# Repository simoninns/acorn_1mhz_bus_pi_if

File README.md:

# Overview
This project provides a Pi Zero hat which allows a Raspberry Pi to be connected to a BBC Micro or Master via the 1 MHz bus port.  The hat is compatible with all versions of the Raspberry Pi (with 40 pin GPIO headers)

Since the BBC Micro is 5Vs and the Pi is 3.3Vs bi-directional level shifting is required.  In addition, the board provides an active audio buffer to allow the Pi Zero to output audio via the GPIO header.  Audio is routed into the BBC Micro if the audio jack isn't required.

# Production
Production files for JLCPCB.com are included for both the PCB and component assembly.  A custom DRC is also included that checks the project files against JLC's production rules.  Production files can be found in the repo:

https://github.com/simoninns/acorn_1mhz_bus_pi_if/tree/main/kicad/jlcpcb

# Use with Raspberry Pi 3B+
Some Raspberry Pi models will not boot due to leakage on the 3.3V rails - the project provides a jumper that can be set if you want to use on of the affected models.  JP3 pins 1 to 2 should be cut and a solder blob placed on 2-3.  Please see the schematic for details.

# Removal of active audio
To lower production cost the on-board LDO and buffer ICs can be omitted (as well as the audio jack).  Bridging JP1 and JP2 will bypass the active components and provide only a passive audio filter (this works fine but provides a poorer sound quality).

## Project status
This project is at first release.  Please read the wiki and see YouTube for consruction videos (detailed in the wiki also).

## Author
This project is designed and maintained by Simon Inns with help from Dominic Plunkett and Daniel Jameson.

## Software License (GPLv3)

    This is free software: you can redistribute it and/or modify
    it under the terms of the GNU General Public License as published by
    the Free Software Foundation, either version 3 of the License, or
    (at your option) any later version.

    Valiant Turtle 2 is distributed in the hope that it will be useful,
    but WITHOUT ANY WARRANTY; without even the implied warranty of
    MERCHANTABILITY or FITNESS FOR A PARTICULAR PURPOSE.  See the
    GNU General Public License for more details.

    You should have received a copy of the GNU General Public License
    along with this program.  If not, see <http://www.gnu.org/licenses/>.

## Hardware License (Creative Commons BY-SA 4.0)
Please see the following link for details: https://creativecommons.org/licenses/by-sa/4.0/

You are free to:

Share - copy and redistribute the material in any medium or format
Adapt - remix, transform, and build upon the material
for any purpose, even commercially.

This license is acceptable for Free Cultural Works.

The licensor cannot revoke these freedoms as long as you follow the license terms.

Under the following terms:

Attribution - You must give appropriate credit, provide a link to the license, and indicate if changes were made. You may do so in any reasonable manner, but not in any way that suggests the licensor endorses you or your use.

ShareAlike - If you remix, transform, or build upon the material, you must distribute your contributions under the same license as the original.

No additional restrictions - You may not apply legal terms or technological measures that legally restrict others from doing anything the license permits.

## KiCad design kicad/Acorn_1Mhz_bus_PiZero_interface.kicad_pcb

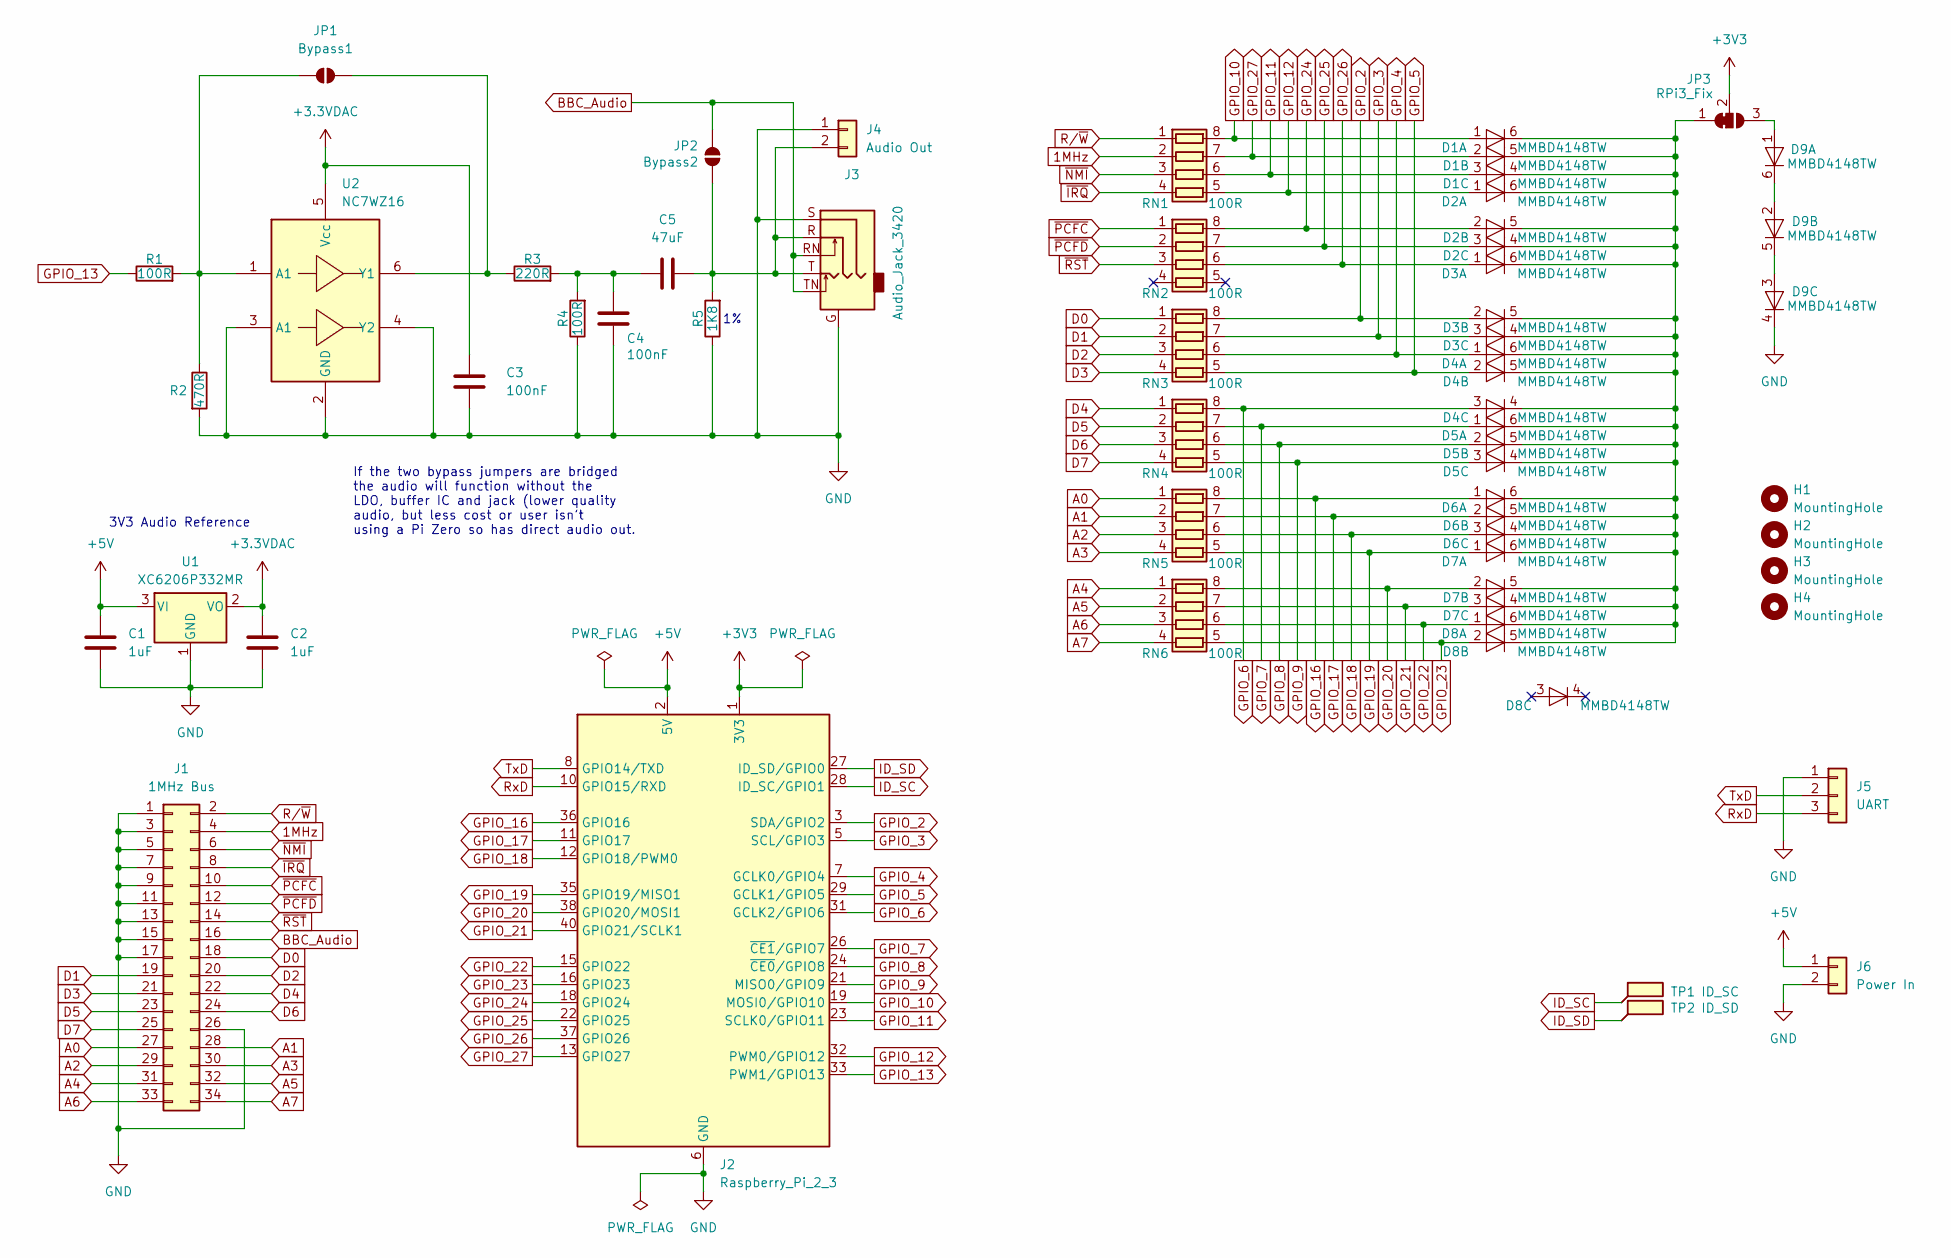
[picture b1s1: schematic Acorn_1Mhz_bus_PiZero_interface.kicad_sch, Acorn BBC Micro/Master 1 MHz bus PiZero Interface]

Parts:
C1, C2: 1uF; C_0603_1608Metric; LCSC C15849
C3, C4: 100nF; C_0603_1608Metric; LCSC C14663
C5: 47uF; C_0603_1608Metric; LCSC C140782
D1, D2, D3, D4, D5, D6, D7, D8, D9: MMBD4148TW; SOT-363_SC-70-6; LCSC C157538
H1, H2, H3, H4: MountingHole; MountingHole_2.7mm_M2.5_DIN965
J1: 1MHz Bus; IDC-Header_2x17_P2.54mm_Vertical; LCSC C20920
J2: Raspberry_Pi_2_3; PinSocket_2x20_P2.54mm_Vertical
J3: Audio_Jack_3420; PJ-3420-X-SMT; LCSC C319102
J4: Audio Out; PinHeader_1x02_P2.54mm_Vertical
J5: UART; PinHeader_1x03_P2.54mm_Vertical
J6: Power In; JST_EH_S2B-EH_1x02_P2.50mm_Horizontal; LCSC C514173
JP1: Bypass1; SolderJumper-2_P1.3mm_Open_Pad1.0x1.5mm
JP2: Bypass2; SolderJumper-2_P1.3mm_Open_Pad1.0x1.5mm
JP3: RPi3_Fix; SolderJumper-3_P1.3mm_Bridged12_Pad1.0x1.5mm_NumberLabels
R1, R4: 100R; R_0603_1608Metric; LCSC C105588
R2: 470R; R_0603_1608Metric; LCSC C114433
R3: 220R; R_0603_1608Metric; LCSC C107696
R5: 1K8; R_0603_1608Metric; LCSC C113298
RN1, RN2, RN3, RN4, RN5, RN6: 100R; R_Array_Convex_4x0402; LCSC C326873
TP1: ID_SC; TestPoint_Pad_1.0x1.0mm
TP2: ID_SD; TestPoint_Pad_1.0x1.0mm
U1: XC6206P332MR; SOT-23-3; LCSC C5446
U2: NC7WZ16; SOT-363_SC-70-6; LCSC C5207819

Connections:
1MHz: J1.4, RN1.2 (R2.1)
+3.3VDAC: C2.1, C3.1, U1.2 (VO), U2.5 (Vcc)
+3V3: J2.1 (3V3), J2.17 (3V3), JP3.2 (C)
+5V: C1.1, J2.2 (5V), J2.4 (5V), J6.1, U1.3 (VI)
A0: J1.27, RN5.1 (R1.1)
A1: J1.28, RN5.2 (R2.1)
A2: J1.29, RN5.3 (R3.1)
A3: J1.30, RN5.4 (R4.1)
A4: J1.31, RN6.1 (R1.1)
A5: J1.32, RN6.2 (R2.1)
A6: J1.33, RN6.3 (R3.1)
A7: J1.34, RN6.4 (R4.1)
BBC_Audio: J1.16, J3.RN, J3.TN, JP2.2 (B)
D0: J1.18, RN3.1 (R1.1)
D1: J1.19, RN3.2 (R2.1)
D2: J1.20, RN3.3 (R3.1)
D3: J1.21, RN3.4 (R4.1)
D4: J1.22, RN4.1 (R1.1)
D5: J1.23, RN4.2 (R2.1)
D6: J1.24, RN4.3 (R3.1)
D7: J1.25, RN4.4 (R4.1)
GND: C1.2, C2.2, C3.2, C4.2, D9.4 (K), J1.1, J1.3, J1.5, J1.7, J1.9, J1.11, J1.13, J1.15, J1.17, J1.26, J2.6 (GND), J2.9 (GND), J2.14 (GND), J2.20 (GND), J2.25 (GND), J2.30 (GND), J2.34 (GND), J2.39 (GND), J3.G, J3.S, J4.1, J5.1, J6.2, R2.2, R4.1, R5.1, U1.1 (GND), U2.2 (GND), U2.3 (A1), U2.4 (Y2)
GPIO_2: D3.2 (A), J2.3 (SDA/GPIO2), RN3.8 (R1.2)
GPIO_3: D3.3 (A), J2.5 (SCL/GPIO3), RN3.7 (R2.2)
GPIO_4: D4.1 (A), J2.7 (GCLK0/GPIO4), RN3.6 (R3.2)
GPIO_5: D4.2 (A), J2.29 (GCLK1/GPIO5), RN3.5 (R4.2)
GPIO_6: D4.3 (A), J2.31 (GCLK2/GPIO6), RN4.8 (R1.2)
GPIO_7: D5.1 (A), J2.26 (~CE1/GPIO7), RN4.7 (R2.2)
GPIO_8: D5.2 (A), J2.24 (~CE0/GPIO8), RN4.6 (R3.2)
GPIO_9: D5.3 (A), J2.21 (MISO0/GPIO9), RN4.5 (R4.2)
GPIO_10: D1.1 (A), J2.19 (MOSI0/GPIO10), RN1.8 (R1.2)
GPIO_11: D1.3 (A), J2.23 (SCLK0/GPIO11), RN1.6 (R3.2)
GPIO_12: D2.1 (A), J2.32 (PWM0/GPIO12), RN1.5 (R4.2)
GPIO_13: J2.33 (PWM1/GPIO13), R1.1
GPIO_16: D6.1 (A), J2.36 (GPIO16), RN5.8 (R1.2)
GPIO_17: D6.2 (A), J2.11 (GPIO17), RN5.7 (R2.2)
GPIO_18: D6.3 (A), J2.12 (GPIO18/PWM0), RN5.6 (R3.2)
GPIO_19: D7.1 (A), J2.35 (GPIO19/MISO1), RN5.5 (R4.2)
GPIO_20: D7.2 (A), J2.38 (GPIO20/MOSI1), RN6.8 (R1.2)
GPIO_21: D7.3 (A), J2.40 (GPIO21/SCLK1), RN6.7 (R2.2)
GPIO_22: D8.1 (A), J2.15 (GPIO22), RN6.6 (R3.2)
GPIO_23: D8.2 (A), J2.16 (GPIO23), RN6.5 (R4.2)
GPIO_24: D2.2 (A), J2.18 (GPIO24), RN2.8 (R1.2)
GPIO_25: D2.3 (A), J2.22 (GPIO25), RN2.7 (R2.2)
GPIO_26: D3.1 (A), J2.37 (GPIO26), RN2.6 (R3.2)
GPIO_27: D1.2 (A), J2.13 (GPIO27), RN1.7 (R2.2)
ID_SC: J2.28 (ID_SC/GPIO1), TP1.1
ID_SD: J2.27 (ID_SD/GPIO0), TP2.1
unnamed: C4.1, C5.1, R3.2, R4.2
unnamed: D1.4 (K), D1.5 (K), D1.6 (K), D2.4 (K), D2.5 (K), D2.6 (K), D3.4 (K), D3.5 (K), D3.6 (K), D4.4 (K), D4.5 (K), D4.6 (K), D5.4 (K), D5.5 (K), D5.6 (K), D6.4 (K), D6.5 (K), D6.6 (K), D7.4 (K), D7.5 (K), D7.6 (K), D8.5 (K), D8.6 (K), JP3.1 (A)
unnamed: D9.1 (A), JP3.3 (B)
unnamed: D9.2 (A), D9.6 (K)
unnamed: D9.3 (A), D9.5 (K)
unnamed: C5.2, J3.R, J3.T, J4.2, JP2.1 (A), R5.2
unnamed: JP1.1 (A), R1.2, R2.1, U2.1 (A1)
unnamed: JP1.2 (B), R3.1, U2.6 (Y1)
RxD: J2.10 (GPIO15/RXD), J5.3
R/~W: J1.2, RN1.1 (R1.1)
TxD: J2.8 (GPIO14/TXD), J5.2
~IRQ: J1.8, RN1.4 (R4.1)
~NMI: J1.6, RN1.3 (R3.1)
~PCFC: J1.10, RN2.1 (R1.1)
~PCFD: J1.12, RN2.2 (R2.1)
~RST: J1.14, RN2.3 (R3.1)

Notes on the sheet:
If the two bypass jumpers are bridged the audio will function without the LDO, buffer IC and jack (lower quality audio, but less cost or user isn't using a Pi Zero so has direct audio out.
3V3 Audio Reference

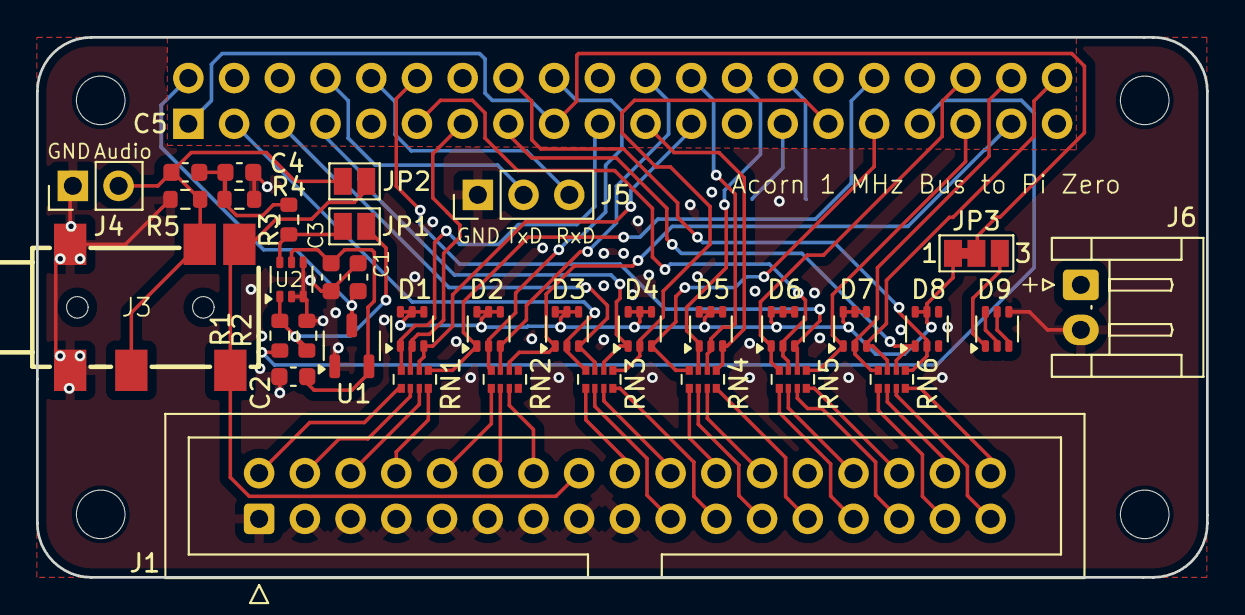
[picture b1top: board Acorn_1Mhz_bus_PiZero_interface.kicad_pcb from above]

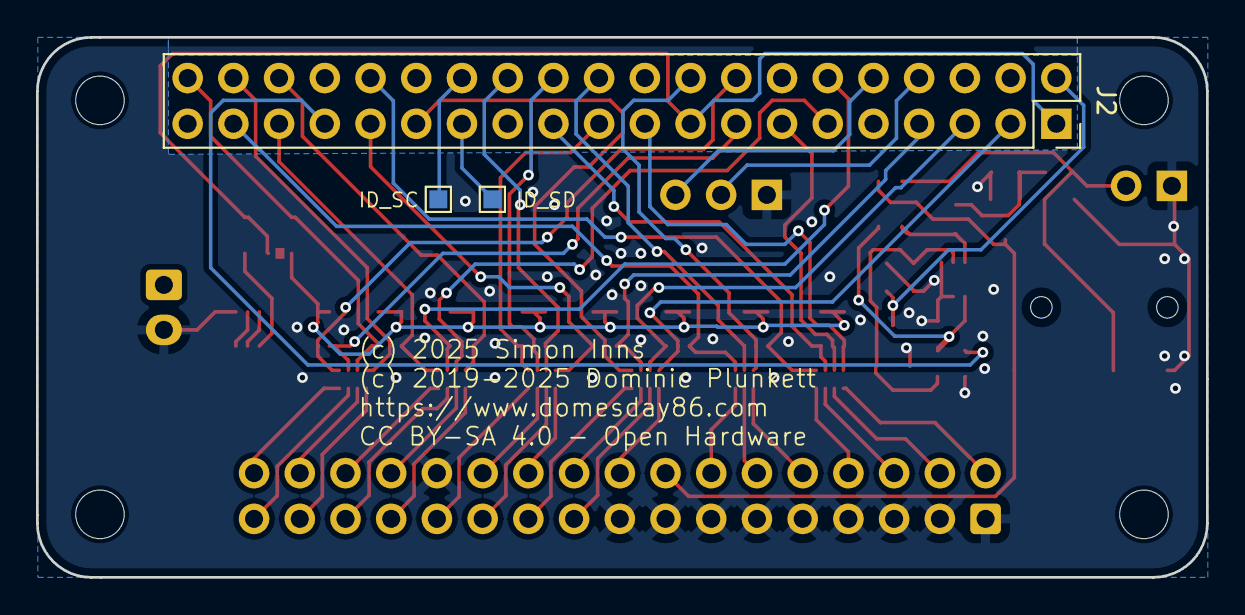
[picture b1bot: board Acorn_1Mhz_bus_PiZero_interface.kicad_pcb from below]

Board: 4 copper layers, 65.0 x 30.0 mm, 42 parts (3 on the bottom side), 64 nets.

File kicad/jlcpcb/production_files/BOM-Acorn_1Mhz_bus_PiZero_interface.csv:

Comment,Designator,Footprint,LCSC,Quantity
100R,"R1,R4",R_0603_1608Metric,C105588,2
220R,R3,R_0603_1608Metric,C107696,1
470R,R2,R_0603_1608Metric,C114433,1
47uF,C5,C_0603_1608Metric,C140782,1
1K8,R5,R_0603_1608Metric,C144686,1
100nF,"C3,C4",C_0603_1608Metric,C14663,2
MMBD4148TW,"D1,D2,D3,D4,D5,D6,D7,D8,D9",SOT-363_SC-70-6,C157538,9
1uF,"C1,C2",C_0603_1608Metric,C15849,2
1MHz Bus,J1,IDC-Header_2x17_P2.54mm_Vertical,C20920,1
Audio_Jack_3420,J3,PJ-3420-X-SMT,C319102,1
100R,"RN1,RN2,RN3,RN4,RN5,RN6",R_Array_Convex_4x0402,C326873,6
Power In,J6,JST_EH_S2B-EH_1x02_P2.50mm_Horizontal,C514173,1
NC7WZ16,U2,SOT-363_SC-70-6,C5207819,1
XC6206P332MR,U1,SOT-23-3,C5446,1

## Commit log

2025-02-10 Basic KiCAD project with partial schematic - checking in before added Pi Zero sub-module
2025-02-10 Completed schematic ready for verification
2025-02-11 Completed schematic and added board file. Basic positioning is done but no routing.
2025-02-11 Got board outline and position of all components. Routing still missing.
2025-02-11 All PCB routing complete - just needs some copper fill
2025-02-11 Flooded and ready for gerber generation - added renderings of front and back of PCB to docs
2025-02-11 Changed board dimensions and redid the routing
2025-02-11 Fixed some DRC warnings around silkscreen text sizes
2025-02-11 Reversed polarity of the power connector. Added BoM spreadsheet with JLCPCB part numbers for assembly
2025-02-12 Added audio in/out test pads
2025-02-12 New schematic design with active audio buffering - schematic not updated
2025-02-12 New design for audio - added footprints (including SMD audio jack)
2025-02-12 Basic layout complete needs routing
2025-02-12 Finished PCB routing a silkscreen - need to track some DRC errors regarding footprints
2025-02-12 DRC issues solved, copper fills completed. Ready for review.
2025-02-12 Added production files for JLCPCB including gerbers and BoM for PCBA service
2025-02-12 Updated JLC files - rotations seem to be broken at the moment
2025-02-12 tweaked routing to improve ground plane
2025-02-13 Fixed small DRC error, produced production files for JLCPCB and verified component placement and rotations. Ready for production.
2025-02-13 Added JLCPCB custom DRC file and corrected PCB against it. Updated README
2025-02-13 Board was rejected due to incorrect 0603x4 RN1-6 parts... this should have been 0402x6. Also the 1K8 resistor was 5% and should be 1%.
2025-02-22 Updated Raspi symbol to use kicad standard library. Added missing mounting holes to schematic. Updated footprints and pulled changes into PCB layout. Aligned M2.5 mounting holes with standard HAT des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
2025-02-22 Updated JLCPCB production files ready for release

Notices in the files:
kicad/Acorn_1Mhz_bus_PiZero_interface.kicad_pcb:
(c) 2025 Simon Inns
(c) 2019-2025 Dominic Plunkett
CC BY-SA 4.0 - Open Hardware
kicad/Acorn_1Mhz_bus_PiZero_interface.kicad_sch:
(c)2025 Simon Inns & (c)2019-2025 Dominic Plunkett
License: Attribution-ShareAlike 4.0 International (CC BY-SA 4.0)
